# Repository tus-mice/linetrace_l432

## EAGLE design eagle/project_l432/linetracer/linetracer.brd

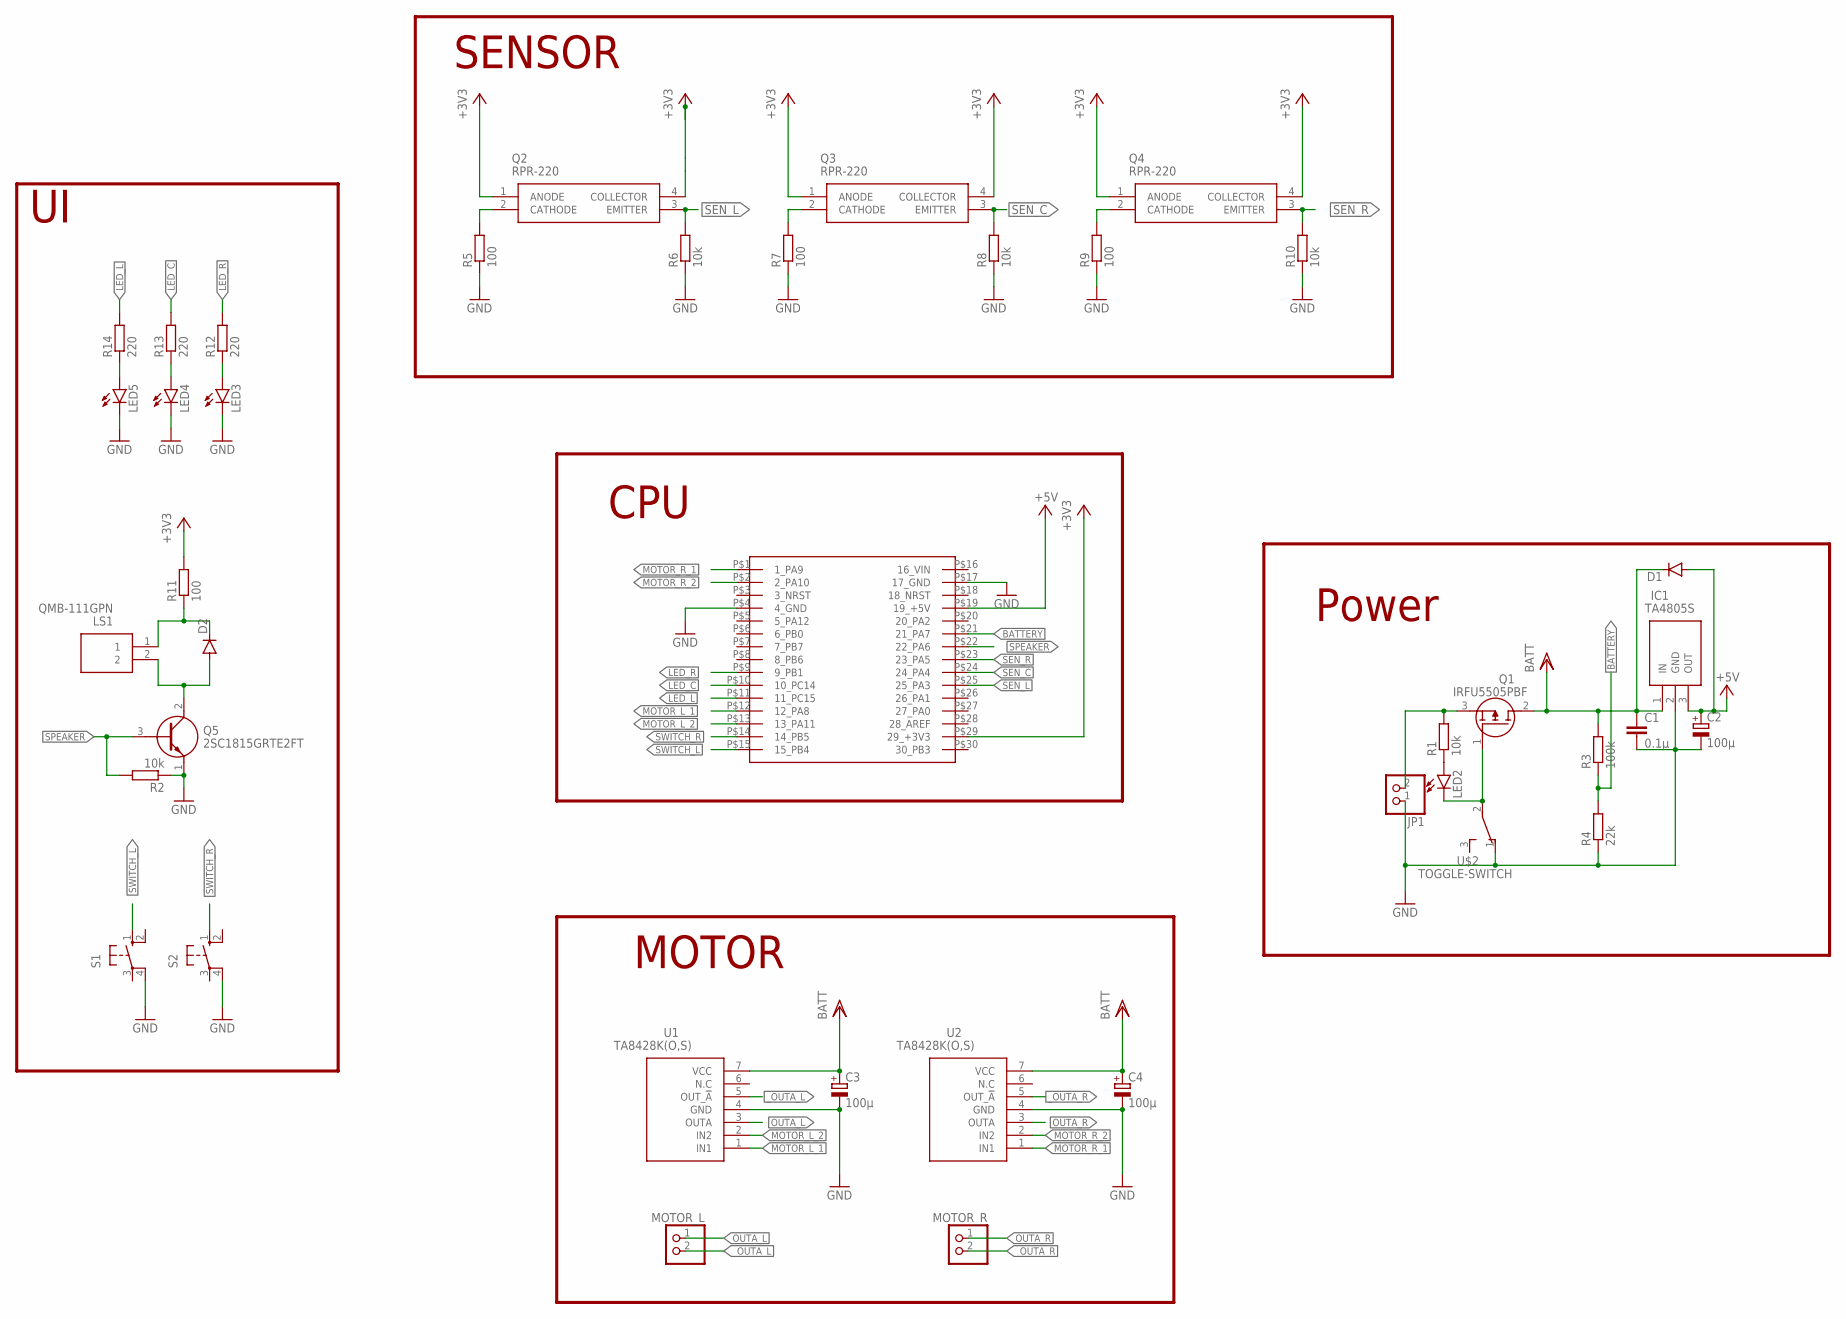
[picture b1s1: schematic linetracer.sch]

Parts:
C1: 0.1μ; C025-024X044
C2, C3, C4: 100μ; E2,5-7
D1, D2: DIODE-D-2.5; D-2.5
IC1: TA4805S; TO230P250X680X1080-3P
JP1: PINHD-1X2; 1X02
LED2, LED3, LED4, LED5: LED3MM
LS1: QMB-111GPN; QMB111GPN
MOTOR_L: PINHD-1X2; 1X02
MOTOR_R: PINHD-1X2; 1X02
Q1: IRFU5505PBF; TO229P239X654X978-3P
Q2, Q3, Q4: RPR-220
Q5: 2SC1815GRTE2FT; 2-5F1B
R1, R2, R6, R8, R10: 10k; 0204V
R3: 100k; 0204V
R4: 22k; 0204V
R5, R7, R9, R11: 100; 0204V
R12, R13, R14: 220; 0204V
S1, S2: 10-XX; B3F-10XX
U1, U2: TA8428K(O,S); HSIP7-P-2.54_1
U$1: NUCLEO_L432KC
U$2: TOGGLE-SWITCH; 1X03

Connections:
16_VIN: U$1.P$16 (16_VIN)
+3V3: Q2.1 (ANODE), Q2.4 (COLLECTOR), Q3.1 (ANODE), Q3.4 (COLLECTOR), Q4.1 (ANODE), Q4.4 (COLLECTOR), R11.2, U$1.P$29 (29_+3V3)
+5V: C2.+, D1.A, IC1.3 (OUT), U$1.P$19 (19_+5V)
BATT: C1.1, C3.+, C4.+, D1.C, IC1.1 (IN), Q1.2 (D), R3.2, U1.7 (VCC), U2.7 (VCC)
BATTERY: R3.1, R4.2, U$1.P$21 (21_PA7)
GND: C1.2, C2.-, C3.-, C4.-, IC1.2 (GND), JP1.1, LED3.K (C), LED4.K (C), LED5.K (C), Q5.1 (E), R2.1, R4.1, R5.1, R6.1, R7.1, R8.1, R9.1, R10.1, S1.4 (P1), S2.4 (P1), U1.4 (GND), U2.4 (GND), U$1.P$4 (4_GND), U$1.P$17 (17_GND), U$2.1
LED_C: R13.2, U$1.P$10 (10_PC14)
LED_L: R14.2, U$1.P$11 (11_PC15)
LED_R: R12.2, U$1.P$9 (9_PB1)
MOTOR_L_1: U1.1 (IN1), U$1.P$12 (12_PA8)
MOTOR_L_2: U1.2 (IN2), U$1.P$13 (13_PA11)
MOTOR_R_1: U2.1 (IN1), U$1.P$1 (1_PA9)
MOTOR_R_2: U2.2 (IN2), U$1.P$2 (2_PA10)
unnamed: JP1.2, Q1.3 (S), R1.2
unnamed: LED2.K (C), Q1.1 (G), U$2.2
unnamed: LED2.A, R1.1
unnamed: D2.C, LS1.1, R11.1
unnamed: Q2.2 (CATHODE), R5.2
unnamed: Q3.2 (CATHODE), R7.2
unnamed: Q4.2 (CATHODE), R9.2
unnamed: D2.A, LS1.2, Q5.2 (C)
unnamed: LED3.A, R12.1
unnamed: LED4.A, R13.1
unnamed: LED5.A, R14.1
OUTA_L: MOTOR_L.1, U1.3 (OUTA)
OUTA_R: MOTOR_R.1, U2.3 (OUTA)
SEN_C: Q3.3 (EMITTER), R8.2, U$1.P$24 (24_PA4)
SEN_L: Q2.3 (EMITTER), R6.2, U$1.P$25 (25_PA3)
SEN_R: Q4.3 (EMITTER), R10.2, U$1.P$23 (23_PA5)
SPEAKER: Q5.3 (B), R2.2, U$1.P$22 (22_PA6)
SWITCH_L: S1.1 (S), U$1.P$15 (15_PB4)
SWITCH_R: S2.1 (S), U$1.P$14 (14_PB5)
_OUTA_L: MOTOR_L.2, U1.5 (OUT_!A)
_OUTA_R: MOTOR_R.2, U2.5 (OUT_!A)

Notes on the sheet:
Power
SENSOR
CPU
MOTOR

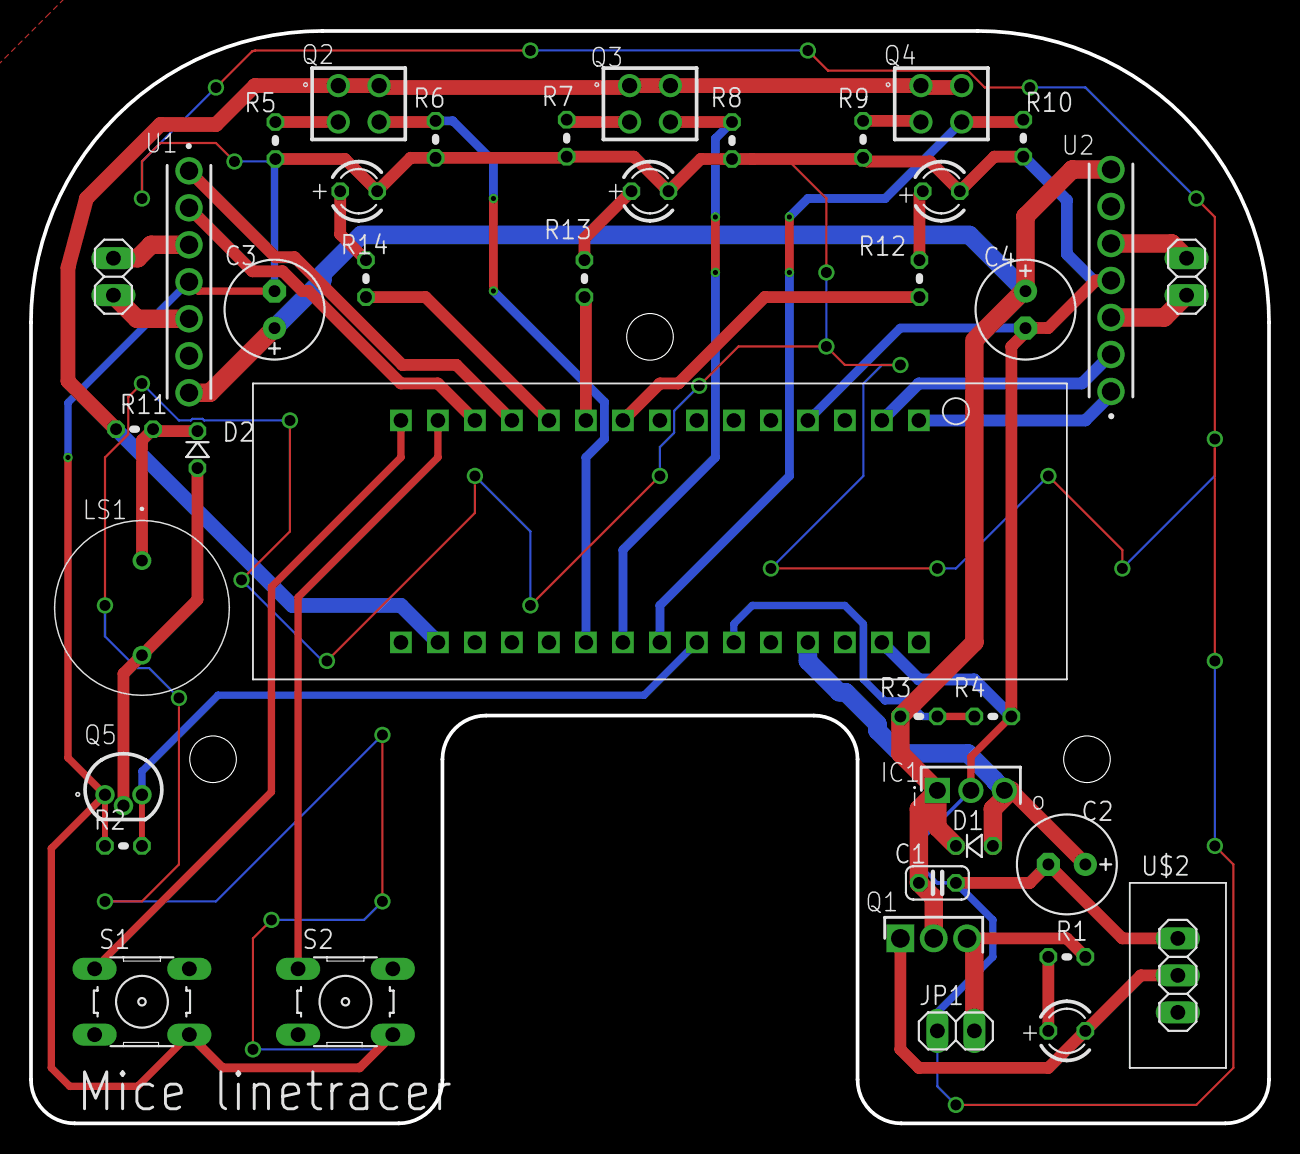
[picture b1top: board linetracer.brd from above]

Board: 2 copper layers, 85.0 x 75.0 mm, 40 parts (0 on the bottom side), 33 nets.

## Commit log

2019-12-07 first:commit
2019-12-07 add:pdf_xsl
2019-12-17 add:pdf
2019-12-17 test
2019-12-17 power
2019-12-18 add:sensor
2019-12-23 schematic
2019-12-30 comp
2019-12-31 add:chassis
